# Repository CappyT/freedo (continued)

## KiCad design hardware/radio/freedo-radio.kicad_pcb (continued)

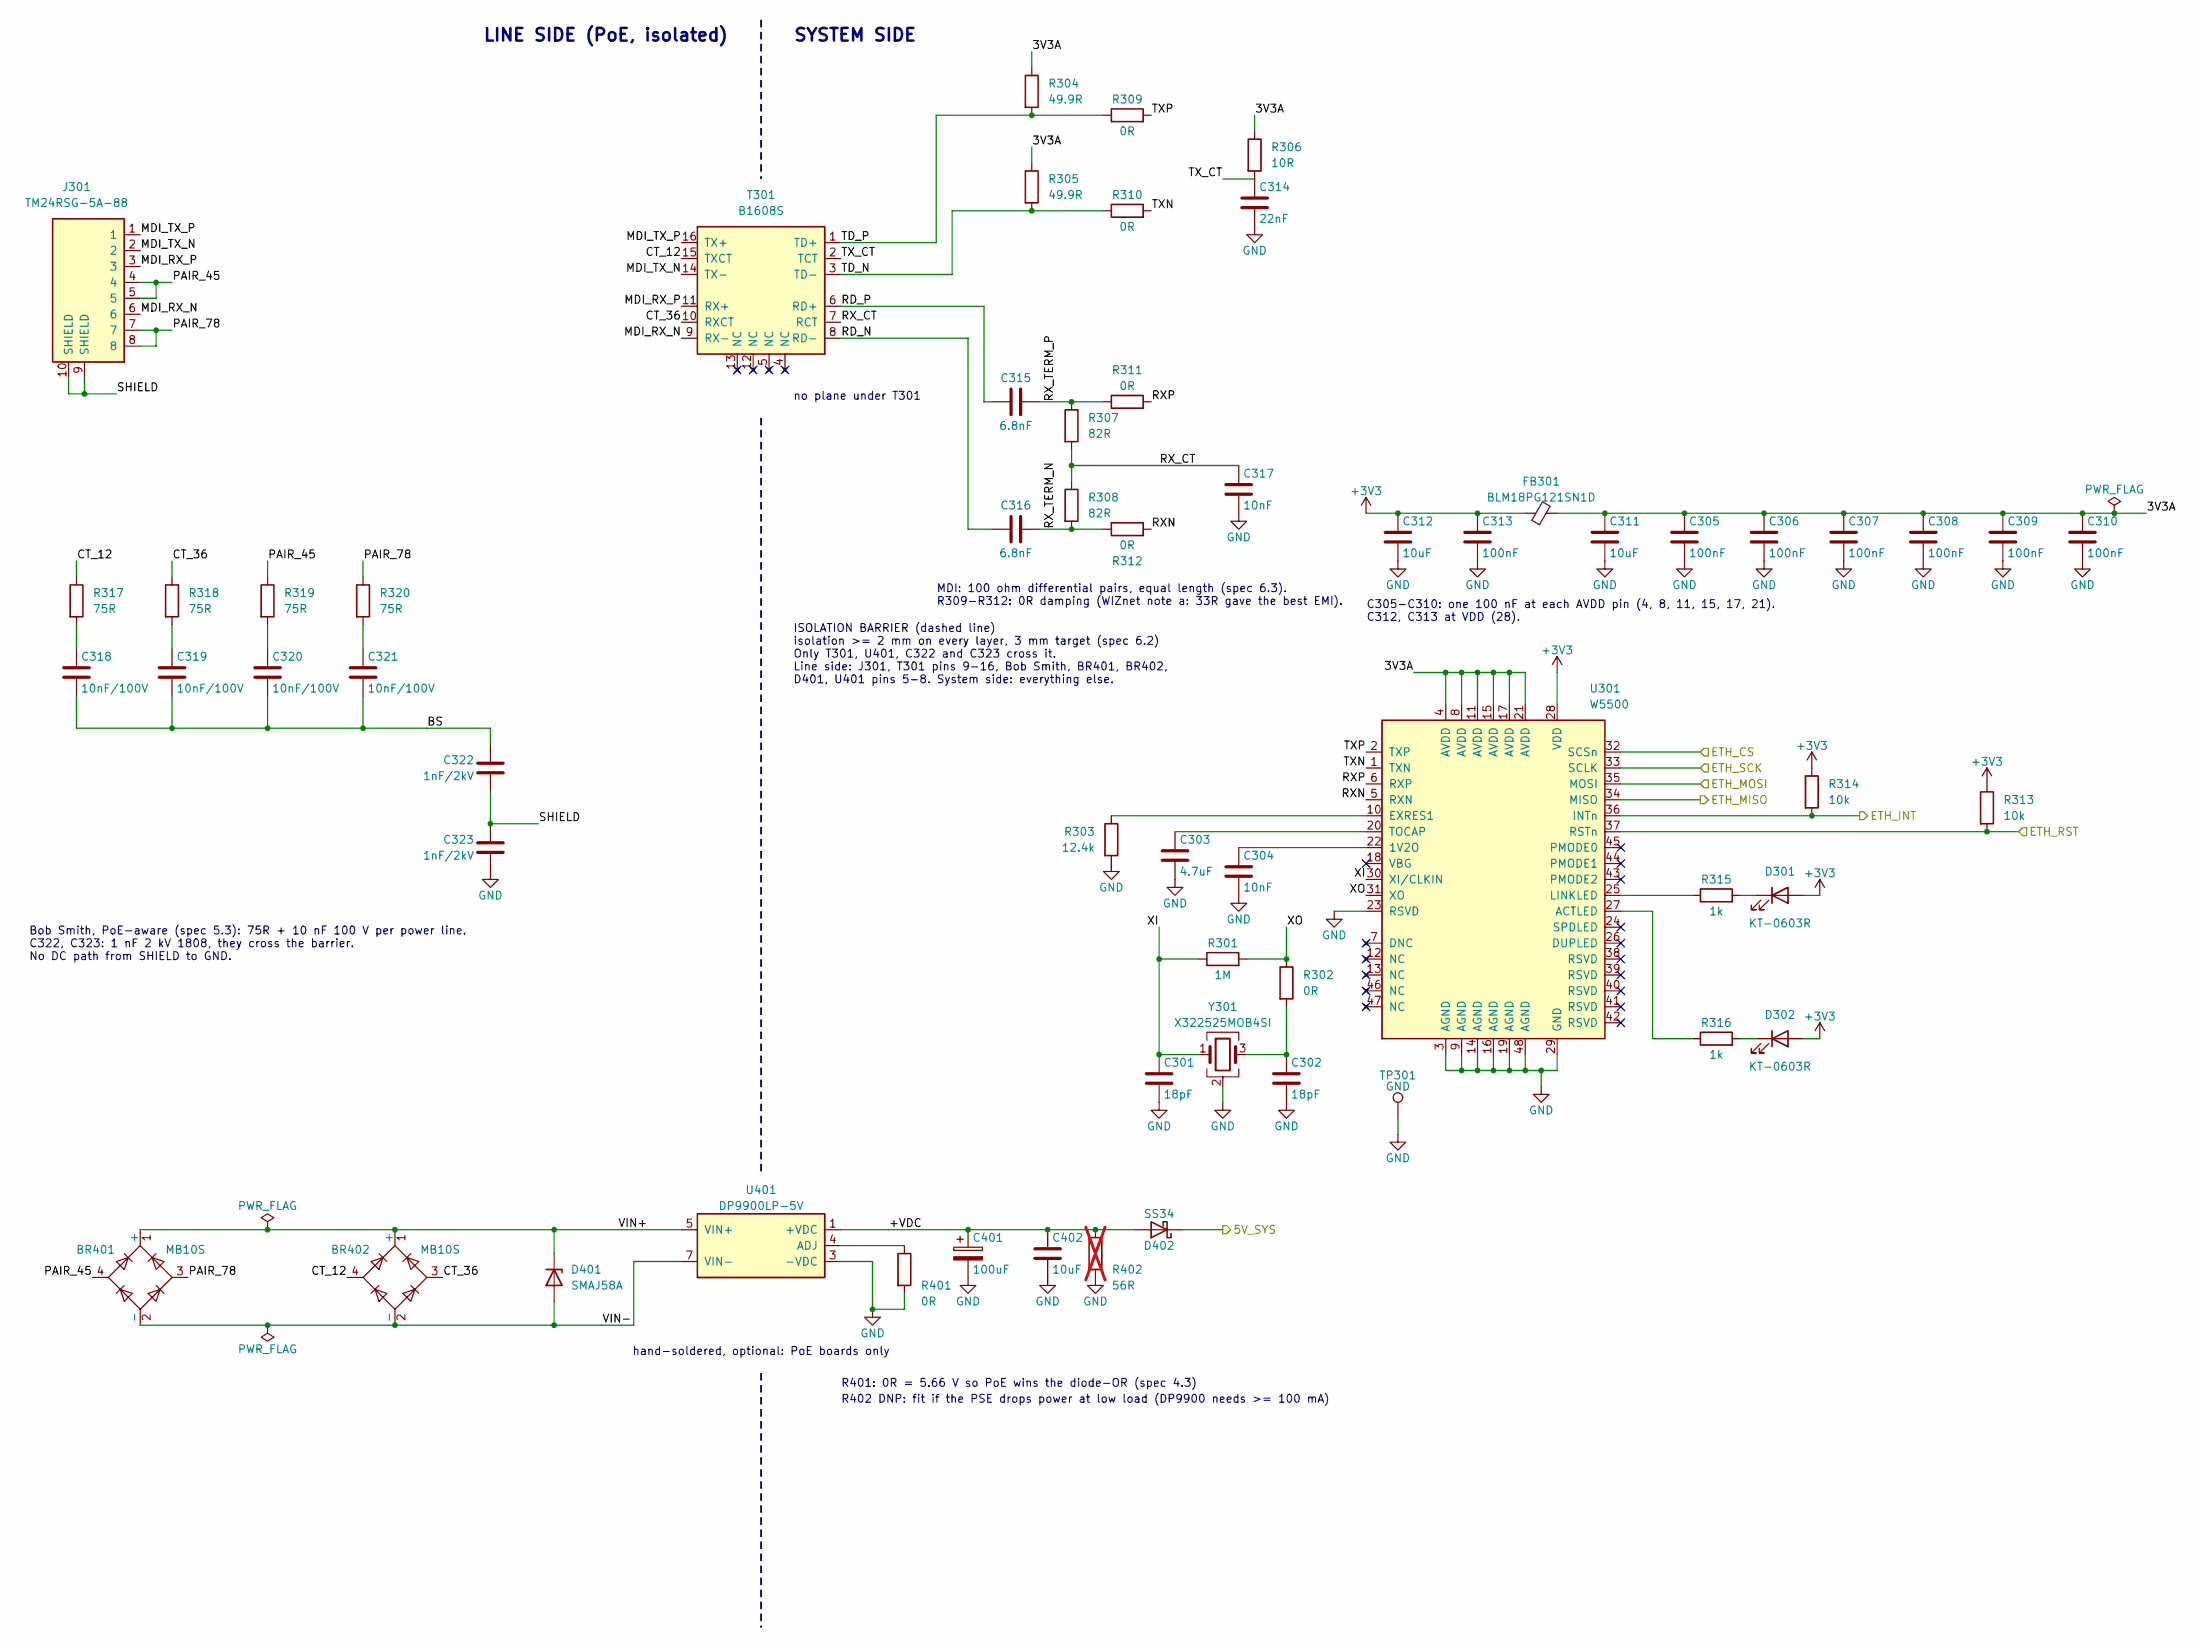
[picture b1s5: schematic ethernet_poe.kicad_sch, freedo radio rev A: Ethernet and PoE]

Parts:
BR401, BR402: MB10S; MBS_L4.7-W3.8-P2.40-LS7.0-TL; MPN MB10S (MDD); LCSC C2488
C301, C302: 18pF; C_0603_1608Metric; MPN CL10C180JB8NNNC; LCSC C1647
C303: 4.7uF; C_0603_1608Metric; MPN CL10A475KO8NNNC; LCSC C19666
C304, C317: 10nF; C_0603_1608Metric; MPN 0603B103K500NT; LCSC C57112
C305, C306, C307, C308, C309, C310, C313: 100nF; C_0603_1608Metric; MPN CC0603KRX7R9BB104; LCSC C14663
C311, C312: 10uF; C_0603_1608Metric; MPN CL10A106KP8NNNC; LCSC C19702
C314: 22nF; C_0603_1608Metric; MPN CL10B223KB8NNNC; LCSC C21122
C315, C316: 6.8nF; C_0603_1608Metric; MPN 0603B682K500NT; LCSC C1631
C318, C319, C320, C321: 10nF/100V; C_0603_1608Metric; MPN 0603B103K101NT; LCSC C43253
C322, C323: 1nF/2kV; C_1808_4520Metric; MPN 1808B102K202NT; LCSC C81332
C401: 100uF; CP_Elec_6.3x7.7; MPN EEHZA1E101XP; LCSC C264047
C402: 10uF; C_0805_2012Metric; MPN CL21A106KAYNNNE; LCSC C15850
D301, D302: KT-0603R; LED_0603_1608Metric; MPN KT-0603R; LCSC C2286
D401: SMAJ58A; SMA_L4.3-W2.6-LS5.2-RD; MPN SMAJ58A (MDD); LCSC C123816
D402: SS34; SMA_L4.3-W2.6-LS5.2-RD; MPN SS34; LCSC C8678
FB301: BLM18PG121SN1D; L_0603_1608Metric; MPN BLM18PG121SN1D; LCSC C14709
J301: TM24RSG-5A-88; RJ45_Hirose_TM24RSG-5A-88; MPN TM24RSG-5A-88; LCSC C6285250
R301: 1M; R_0603_1608Metric; MPN 0603WAF1004T5E; LCSC C22935
R302, R309, R310, R311, R312, R401: 0R; R_0603_1608Metric; MPN 0603WAF0000T5E; LCSC C21189
R303: 12.4k; R_0603_1608Metric; MPN 0603WAF1242T5E; LCSC C22865
R304, R305: 49.9R; R_0603_1608Metric; MPN 0603WAF499JT5E; LCSC C23185
R306: 10R; R_0603_1608Metric; MPN 0603WAF100JT5E; LCSC C22859
R307, R308: 82R; R_0603_1608Metric; MPN 0603WAF820JT5E; LCSC C23255
R313, R314: 10k; R_0603_1608Metric; MPN 0603WAF1002T5E; LCSC C25804
R315, R316: 1k; R_0603_1608Metric; MPN 0603WAF1001T5E; LCSC C21190
R317, R318, R319, R320: 75R; R_0603_1608Metric; MPN 0603WAF750JT5E; LCSC C4275
R402: 56R; R_2512_6332Metric; MPN MCR100JZHJ560; LCSC C308356; not fitted
T301: B1608S; CND-tek_B1608S_SMD-16_P1.27mm; MPN B1608S; LCSC C507596
TP301: GND; TestPoint_Pad_D1.5mm
U301: W5500; LQFP-48_L7.0-W7.0-P0.50-LS9.0-BL; MPN W5500; LCSC C32843
U401: DP9900LP-5V; SDAPO_DP9900LP_THT-8; MPN DP9900LP-5V; LCSC C5380108
Y301: X322525MOB4SI; CRYSTAL-SMD_4P-L3.2-W2.5-BL; MPN X322525MOB4SI; LCSC C9006

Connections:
+3V3: C312.1, C313.1, D301.2 (A), D302.2 (A), FB301.1, R313.1, R314.1, U301.28 (VDD); also elsewhere on the board
/ethernet_poe/3V3A: C305.1, C306.1, C307.1, C308.1, C309.1, C310.1, C311.1, FB301.2, R304.1, R305.1, R306.1, U301.4 (AVDD), U301.8 (AVDD), U301.11 (AVDD), U301.15 (AVDD), U301.17 (AVDD), U301.21 (AVDD)
/ethernet_poe/5V_SYS: D402.1 (K); also elsewhere on the board
/ethernet_poe/+VDC: C401.1, C402.1, D402.2 (A), R402.1, U401.1 (+VDC), U401.2 (+VDC)
/ethernet_poe/BS: C318.2, C319.2, C320.2, C321.2, C322.1
/ethernet_poe/CT_12: BR402.4, R317.1, T301.15 (TXCT)
/ethernet_poe/CT_36: BR402.3, R318.1, T301.10 (RXCT)
/ethernet_poe/ETH_CS: U301.32 (SCSn); also elsewhere on the board
/ethernet_poe/ETH_INT: R314.2, U301.36 (INTn); also elsewhere on the board
/ethernet_poe/ETH_MISO: U301.34 (MISO); also elsewhere on the board
/ethernet_poe/ETH_MOSI: U301.35 (MOSI); also elsewhere on the board
/ethernet_poe/ETH_RST: R313.2, U301.37 (RSTn); also elsewhere on the board
/ethernet_poe/ETH_SCK: U301.33 (SCLK); also elsewhere on the board
/ethernet_poe/MDI_RX_N: J301.6, T301.9 (RX-)
/ethernet_poe/MDI_RX_P: J301.3, T301.11 (RX+)
/ethernet_poe/MDI_TX_N: J301.2, T301.14 (TX-)
/ethernet_poe/MDI_TX_P: J301.1, T301.16 (TX+)
/ethernet_poe/PAIR_45: BR401.4, J301.4, J301.5, R319.1
/ethernet_poe/PAIR_78: BR401.3, J301.7, J301.8, R320.1
/ethernet_poe/RD_N: C316.1, T301.8 (RD-)
/ethernet_poe/RD_P: C315.1, T301.6 (RD+)
/ethernet_poe/RXN: R312.2, U301.5 (RXN)
/ethernet_poe/RXP: R311.2, U301.6 (RXP)
/ethernet_poe/RX_CT: C317.1, R307.2, R308.1, T301.7 (RCT)
/ethernet_poe/RX_TERM_N: C316.2, R308.2, R312.1
/ethernet_poe/RX_TERM_P: C315.2, R307.1, R311.1
/ethernet_poe/SHIELD: C322.2, C323.1, J301.9 (SHIELD), J301.10 (SHIELD), J301.11 (SHIELD), J301.12 (SHIELD), J301.13 (SHIELD), J301.14 (SHIELD)
/ethernet_poe/TD_N: R305.2, R310.1, T301.3 (TD-)
/ethernet_poe/TD_P: R304.2, R309.1, T301.1 (TD+)
/ethernet_poe/TXN: R310.2, U301.1 (TXN)
/ethernet_poe/TXP: R309.2, U301.2 (TXP)
/ethernet_poe/TX_CT: C314.1, R306.2, T301.2 (TCT)
/ethernet_poe/VIN+: BR401.1 (+), BR402.1 (+), D401.1 (K), U401.5 (VIN+), U401.6 (VIN+)
/ethernet_poe/VIN-: BR401.2 (-), BR402.2 (-), D401.2 (A), U401.7 (VIN-), U401.8 (VIN-)
/ethernet_poe/XI: C301.1, R301.1, U301.30 (XI/CLKIN), Y301.1
/ethernet_poe/XO: R301.2, R302.1, U301.31 (XO)
GND: C301.2, C302.2, C303.2, C304.2, C305.2, C306.2, C307.2, C308.2, C309.2, C310.2, C311.2, C312.2, C313.2, C314.2, C317.2, C323.2, C401.2, C402.2, R303.2, R401.2, R402.2, TP301.1, U301.3 (AGND), U301.9 (AGND), U301.14 (AGND), U301.16 (AGND), U301.19 (AGND), U301.23 (RSVD), U301.29 (GND), U301.48 (AGND), U401.3 (-VDC), Y301.2 (G), Y301.4 (G); also elsewhere on the board
unnamed: C302.1, R302.2, Y301.3
unnamed: C318.1, R317.2
unnamed: C319.1, R318.2
unnamed: C320.1, R319.2
unnamed: C321.1, R320.2
unnamed: D301.1 (K), R315.2
unnamed: D302.1 (K), R316.2
unnamed: C304.1, U301.22 (1V2O)
unnamed: R316.1, U301.27 (ACTLED)
unnamed: R303.1, U301.10 (EXRES1)
unnamed: R315.1, U301.25 (LINKLED)
unnamed: C303.1, U301.20 (TOCAP)
unnamed: R401.1, U401.4 (ADJ)

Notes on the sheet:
LINE SIDE (PoE, isolated)
SYSTEM SIDE
ISOLATION BARRIER (dashed line) isolation >= 2 mm on every layer, 3 mm target (spec 6.2) Only T301, U401, C322 and C323 cross it. Line side: J301, T301 pins 9-16, Bob Smith, BR401, BR402, D401, U401 pins 5-8. System side: everything else.
no plane under T301
hand-soldered, optional: PoE boards only
R401: 0R = 5.66 V so PoE wins the diode-OR (spec 4.3)
Bob Smith, PoE-aware (spec 5.3): 75R + 10 nF 100 V per power line. C322, C323: 1 nF 2 kV 1808, they cross the barrier. No DC path from SHIELD to GND.
C305-C310: one 100 nF at each AVDD pin (4, 8, 11, 15, 17, 21). C312, C313 at VDD (28).
MDI: 100 ohm differential pairs, equal length (spec 6.3). R309-R312: 0R damping (WIZnet note a: 33R gave the best EMI).
R402 DNP: fit if the PSE drops power at low load (DP9900 needs >= 100 mA)

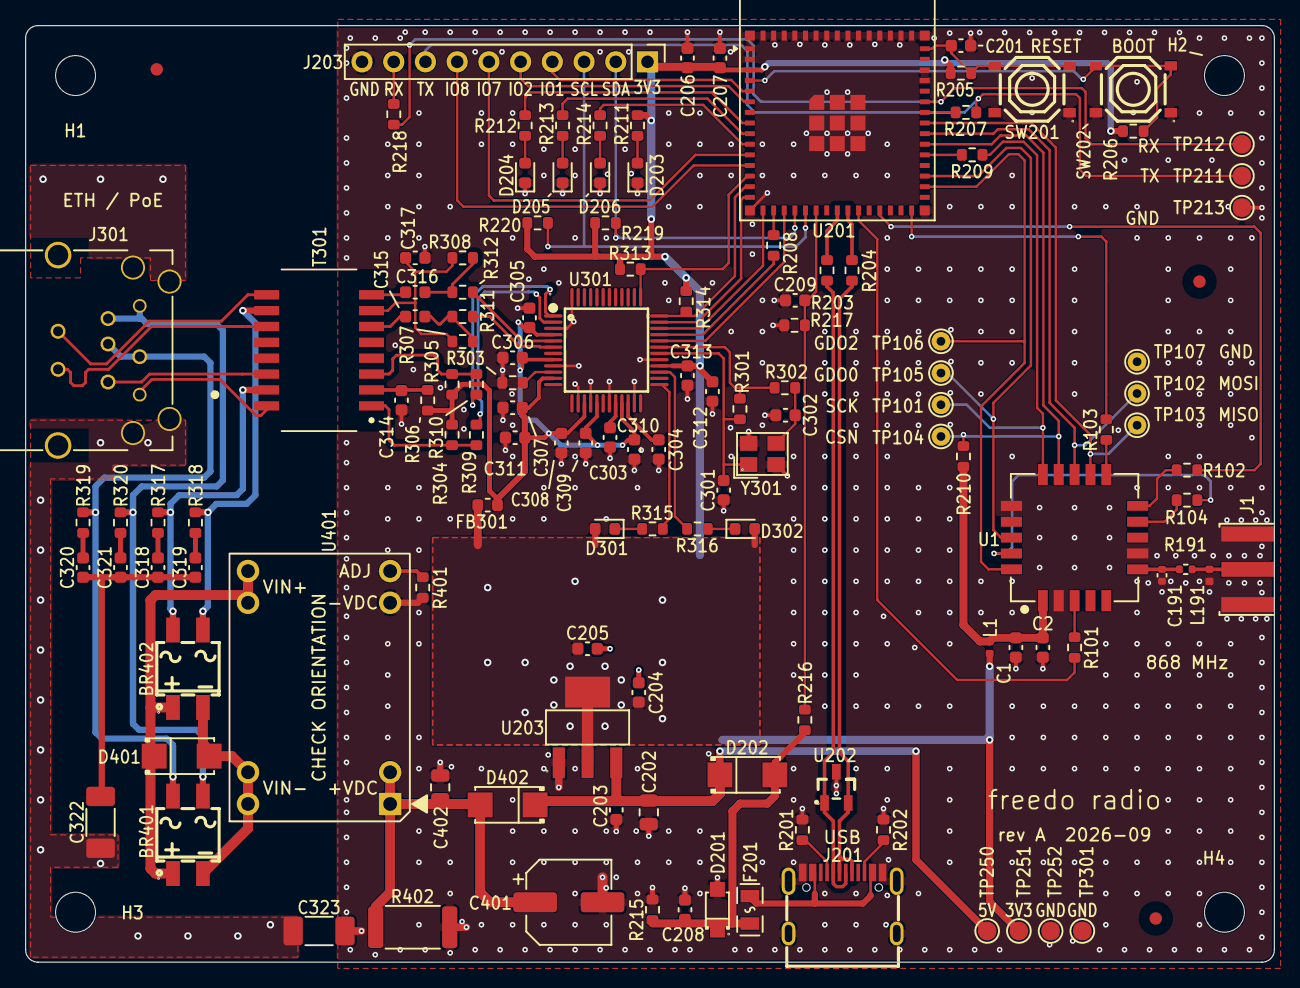
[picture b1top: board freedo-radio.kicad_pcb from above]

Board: 4 copper layers, 100.0 x 75.0 mm, 135 parts (0 on the bottom side), 97 nets.

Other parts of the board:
FID1, FID2, FID3: Fiducial; Fiducial_1mm_Mask2mm
H1, H2, H3, H4: MountingHole_3.2mm_M3
